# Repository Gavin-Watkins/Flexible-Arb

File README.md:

# Flexible Arduino Due based Arbitrary Signal Generator
Often during a project I have needed a complex test signal that is beyond the capability of the signal or function generators available in my lab. Commercial arbitrary signal generators (ARB) consisting of a fast memory coupled to a digital-to-analogue converter (DAC) are available, but often do not offer the right mix of analog and digital outputs in a suitably flexible (and affordable!) form. This has also been a problem during my day job where I have need to drive a high efficiency radio frequency (RF) power amplifiers (PA) or transmitters with two analogue outputs for the in-phase (I) and quadrature (Q) inputs of an RF modulator and several digital outputs for switching parts of the transmitter. [Previous work used an ARB platform developed around an Arduino Mega2560](https://www.researchgate.net/publication/361063526_A_Digital_Power_Amplifier_for_32-QAM). This was limited to a sample rate of 457kS/s. To increase the sample rate a new ARB has been developed based on an Arduino Due offering up to 8.4MS/s.

The Arduino Due is based on the 32-bit ATSAM3X8E allowing multiple 8-bit DACs and digital outputs to be mapped onto a single port. This ensuring all DAC or digital outputs update at the same time and only a single LUT is call for every update. The Arduino Due also runs at a higher clock rate of 84 MHz. Although 32-bit, none of the four ports (A to D) available on the ATSAM3X8E’s pins map to all 32-bits. Of the four ports, C with 24-bits available is the most useful. These 24 bits in this project are connected to two 8-bit DACs and one 8-bit digital port. However, they could for example drive two 12-bit DACs or any such combination.

# Testing the Arduino Due
The first thing anyone looks at with an ARB is the sampling rate. In a software based ARB like this (as oppose to an FPGA implementation) the microprocessor much fetch the output samples from memory and present them to the port with the DAC. This takes ten instruction cycles resulting in 8.4 MS/s as shown below in the minimum viable code:

start:                                // start of loop  

count = count + 1;                    // increment counter, takes two instruction

count = count & 0x000000FF;           // mask to prevent overflow from end of LUT, takes one instruction

PIOC->PIO_ODSR = Portvalues[count];   // access the LUT and send it to PortC, takes two instructions

goto start;                           // and repeat, takes five instructions

The felixbility of this option opens up other possiblities, like adding a second port which reads from its own LUT. PortA offers 23 bits, which would give a total of 47bits of data. This would however slow down the sample rate to 5.25 MS/s and require external latches for synchronising the data. This ran fastest when in Setup. Putting it in Loop resulted in slowing down. Why this is so, I'm not sure, but it is something I intend to explore further.

# DACs
The most important part of any ARB are the DACs. For this I settle on the DAC0801. Although quite old, they are readily available and easy to interface. Their datasheet quotes a settling time of 100ns consisting of the DAC slewing time and that for any ringing at the output to settle. The slewing time is a factor of the DAC output current and its load impedance. This suggests a maximum sample rate of 10 MS/s, which fits well with the 8.4 MS/s of the Due. The DAC0801 has complementary current sink outputs (pins 2 and 4). The datasheet suggests op-amp active current to voltage (I/V) converters as an output stage. This was found to introduce excess ringing, so passive resistive I/V converters were used instead. With a 1kΩ resistive load (RL) the slew rate was 30V/μs equivalent to a rise and fall time of 42ns. 

The DAC (IC1 and IC3) and op-amp (IC2 and IC4) interface is shown in the Eagle schematic "Sch6.sch" and as a png "Sch6.png". The peak output current of the DAC0801 is set at 2.13mA by the 4k7 resistors on pins 14 and 15 (R10, R14, R19 and R20) when a ±10V power supply is used. A 1k1 resistor tied to 0V and two 4k7 resistors in series (9k4) to +10 V positive supply rail add an offset so the output voltage at pin 4 swings positive and negative around 0V. This is a high impedance port so an op-amp with a gain of 2V/V buffers the output to drive 2V peak-to-peak into a 50Ω load. In the prototype a TL071 proved optimal in terms of bandwidth and ringing. Note in the schematic this is listed as a 741, simply because it was the first op-amp listed. The TL071 has a unity gain bandwidth product of 3MHz, reduced to 1.5MHz with a gain of 2V/V. Other op-amps may provide a better combination of bandwidth, slew rate and output current.

# Code
The Arduino Due can be programmed in the usual Arduino IDE, but has a unique set of instructions which allows direct port access. The following commands setup port C of the Due for direct access: PIOC→PIO_PER and PIOC→PIO_OER. The command PIOC→PIO_ODSR is then used to write data to the port. A goto loop sends data from the LUT to Port C runs in the setup, as using the main Void loop incurs various overheads including the I/O system to check the serial port. The result is 10 instructions and 8.4MS/s output rate. The LUT allocations are accessed by the variable count which is a 32-bit integer. This is masked (by ANDing) with FF (256) in the sinewave example, 1FF (512) in the triple test example and 4FFF (16384) for the 4G Long Term Evolution (LTE) signal example. Restricting the LUT to powers of 2 simplifies (and hence speeds up) the code. For other values an IF or FOR loop could be used to reset count at any value. A noInterrupts command to disable interrupts is included as without it jitter was noted on the output waveform suggesting the compiler sets some interrupts by default. If a lower sample frequency is desired though, the delayMicroseconds command can be included. In this case noInterrupts should be commented out.

# Data Generation
The data for all ports and the trigger signal are stored in a single LUT (Portvalues in the code). For Port C, the bits that are available on the external pins are: bits 1-8 for Ch A DAC, bits 12-19 for Ch B DAC, bits 21-26 for a digital interface and bit 28 as a trigger. These are generated individually and then mapped into a 32bit word which forms the values of Portvalues by multiplying the individual values by an offset and adding them together, for example:

Portvalues[X] = 2^28 x Trigger + 2^21 x Digital + 2^12 x DAC2 + 2 x DAC1

# Tool Chain 
The first two examples were generated in an OpenOffice spreadsheet (File "Signal Gen3.ods) as the LUTs were not very big. The third example was in Python ( due to the resulting LUT size. If using a spreadsheet the data will be generated in a single column. This can be copy and pasted directly into the Arduino IDE as a single column array. It is often more practical though to do this as a 2D array. The values from different cells can be combined with commas as a string into a single cell using the “&” function. In the sinewave example where the values of column Y are to be reformatted into a 16 column by 16 row for 256 values the following is used:

=Y2 & " , " & Y3 & ", " & Y4 & ", " & Y5 & ", " & Y6 & ", " & Y7 & ", " & Y8 & ", " & Y9 & ", " & Y10 & ", " & Y11 & ", " & Y12 & ", " & Y13 & ", " & Y14 & ", " & Y15 & ", " & Y16 & ", " & Y17 & ", "

Using the autofill function will not appropriately increment the Y column values, so there is still quite a bit of manual processing to be done, which is why for larger arrays it is appropriate to use Python. The Python code reads in the File "1M4LTE.txt". The sample rate of the LTE data is 7.68 MS/s, this is the original 122.88 MS/s downsampled by 16. Adding a dummy instruction to the Arduino code results in a sample rate of 7.64 MS/s. This is not close enough to 7.68 MS/s for standard compliance, but sufficient for measuring the adjacent channel power ratio (ACPR) of a PA/transmitter output.

# Hardware Implementation
To verify the concept, an Arduino Due “shield” was produced. This was fabricated on standard FR4 substrate using through hole DIL components. The layout is shown in "Sch6.brd" for Eagle and "Sch6_PCB.png" as a png. The Gerber files are in the zip file "Gerbers.zip". DIL components incur stray inductance and capacitance when operating in the MHz region, but allow the design to be easily modified. A surface mount implementation would probably produce better results than those presented here. 

The shield runs off a 5V supply for the digital and +/-10V for the analogue. The former can be extracted from the USB interface, as it is assumed that this project will be permanently connected to a computer for updating the LUT. The +/-10V can be derived from the 5V USB with a DC-DC converter and then smoothing and filtering.

# Example Results
The code includes three examples: a 32.8125kHz quadrature sinewave on DAC1 and DAC2 with a 256 value LUT (8.4MS/s / 256 = 32.8125 kHz), a triple tone test at around 1 MHz and the 4G LTE signal generation. Screen captures of these are shown to demonstrate the capabilities of the ARB. For the triple tone test the three tone frequencies are 984.375 kHz, 1.00078125 MHz and 1.0171875 MHz. These three resulting frequencies (Fr) were calculated with:

Fr = Fs * n / LUTs

Where Fs is the sampling frequency, n a whole number to avoid discontinuities – reducing spurious produces – and LUTs the LUT size. For an Fs was 8.4MS/s, n: 60, 61 and 62, and LUTs 512. Even with all the harmonically related spurious products, they are -38dB relative to the three tones. A higher resolution DAC would offer greater dynamic range, and hence lower spurious products. 

For the LTE signal, a screen capture of the spectrum of the I-channel signal is included. This includes guard channels, resulting in an actual RF bandwidth is 1.08MHz (consisting of six 180kHz resource blocks). The baseband bandwidth is half this, a spectrum of 504kHz as clearly shown in the example. The spectral regrowth is partially due to DAC non-linearities and also spurious products introduced by the system. uffers. The next phase of this research is to combine the LTE signal generator with a low-cost quadrature modulator development board to generate 4G signals for testing transmitter architectures.

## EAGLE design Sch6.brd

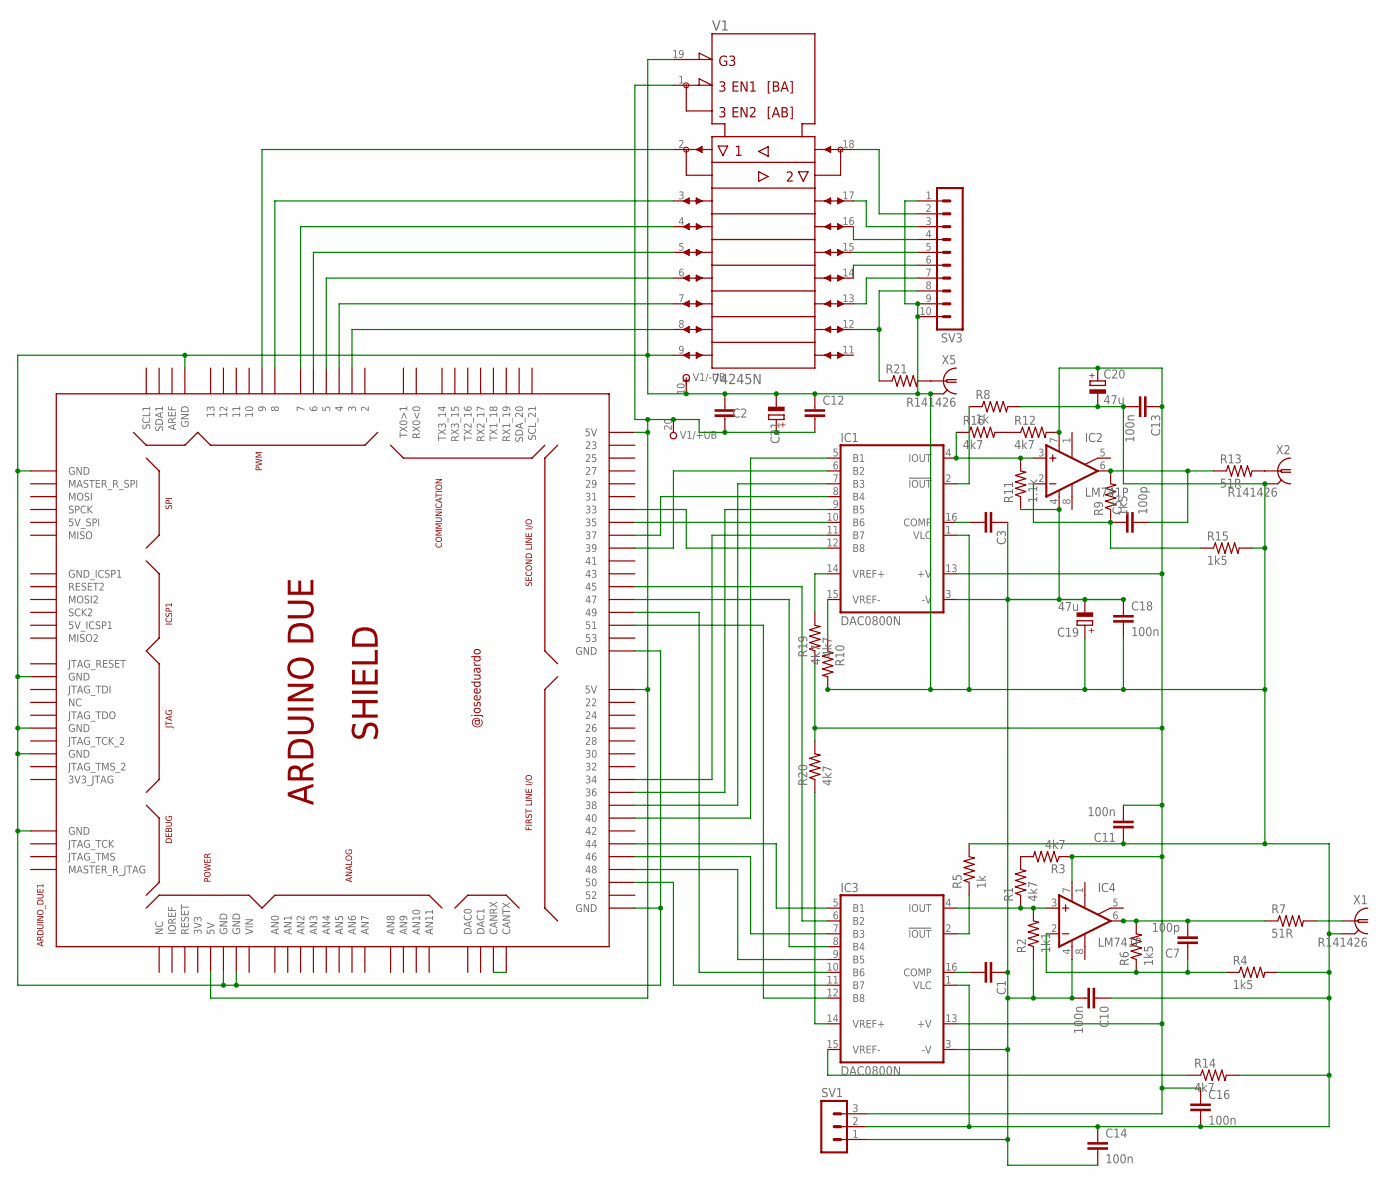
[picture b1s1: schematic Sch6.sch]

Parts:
ARDUINO_DUE1: ARDUINO_DUE_SHIELD
C1, C2, C3, C12: C-EU050-025X075; C050-025X075
C5, C7: 100p; C050-025X075
C10, C11, C13, C14, C16, C18: 100n; C050-025X075
C19, C20: 47u; E5-10,5
C21: CPOL-EUE5-10.5; E5-10,5
IC1, IC3: DAC0800N; DIL16
IC2, IC4: LM741P; DIL08
R1, R3, R10, R12, R14, R16, R19, R20: 4k7; 0207/10
R2: 1k1; 0207/10
R4, R6, R9, R15: 1k5; 0207/10
R5, R8: 1k; 0207/10
R7, R13: 51R; 0207/10
R11: 1.1k; 0207/10
R21: R-US_0207/10; 0207/10
SV1: MA03-1
SV3: MA10-1
V1: 74245N; DIL20
X1, X2, X5: R141426

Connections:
unnamed: ARDUINO_DUE1.51, IC3.12 (B8)
unnamed: R21.2, X5.1
unnamed: ARDUINO_DUE1.33, IC1.12 (B8)
unnamed: IC1.2 (!IOUT), R8.1
unnamed: ARDUINO_DUE1.9, V1.2 (A1)
unnamed: ARDUINO_DUE1.34, IC1.11 (B7)
unnamed: ARDUINO_DUE1.50, IC3.11 (B7)
unnamed: ARDUINO_DUE1.35, IC1.10 (B6)
unnamed: ARDUINO_DUE1.36, IC1.9 (B5)
unnamed: ARDUINO_DUE1.37, IC1.8 (B4)
unnamed: ARDUINO_DUE1.49, IC3.10 (B6)
unnamed: ARDUINO_DUE1.CANRX, ARDUINO_DUE1.CANTX
unnamed: ARDUINO_DUE1.5V0 (5V), ARDUINO_DUE1.5V0_1 (5V), ARDUINO_DUE1.5V0_2 (5V), C2.2, C12.2, C21.+, V1.1 (DIR), V1.20 (+UB)
unnamed: ARDUINO_DUE1.38, IC1.7 (B3)
unnamed: ARDUINO_DUE1.39, IC1.6 (B2)
unnamed: ARDUINO_DUE1.8, V1.3 (A2)
unnamed: ARDUINO_DUE1.40, IC1.5 (B1)
unnamed: ARDUINO_DUE1.48, IC3.9 (B5)
unnamed: ARDUINO_DUE1.47, IC3.8 (B4)
unnamed: R1.2, R3.2
unnamed: ARDUINO_DUE1.45, IC3.6 (B2)
unnamed: IC3.4 (IOUT), IC4.3 (+IN), R1.1, R2.2
unnamed: ARDUINO_DUE1.7, V1.4 (A3)
unnamed: ARDUINO_DUE1.6, V1.5 (A4)
unnamed: ARDUINO_DUE1.5, V1.6 (A5)
unnamed: ARDUINO_DUE1.4, V1.7 (A6)
unnamed: ARDUINO_DUE1.3, V1.8 (A7)
unnamed: SV3.5, V1.15 (B4)
unnamed: SV3.6, V1.14 (B5)
unnamed: SV3.7, V1.13 (B6)
unnamed: R21.1, SV3.8, V1.12 (B7)
unnamed: SV3.4, V1.16 (B3)
unnamed: SV3.3, V1.17 (B2)
unnamed: SV3.2, V1.18 (B1)
unnamed: C11.2, C13.1, C16.1, C20.+, IC1.13 (+V), IC2.7 (V+), IC3.13 (+V), IC4.7 (V+), R3.1, R12.2, R19.1, R20.2, SV1.3
unnamed: ARDUINO_DUE1.GND, ARDUINO_DUE1.GND_1 (GND), ARDUINO_DUE1.GND_2 (GND), ARDUINO_DUE1.GND_3 (GND), ARDUINO_DUE1.GND_4 (GND), ARDUINO_DUE1.GND_5 (GND), ARDUINO_DUE1.GND_7 (GND), ARDUINO_DUE1.GND_8 (GND), ARDUINO_DUE1.GND_9 (GND), ARDUINO_DUE1.GND_10 (GND), C2.1, C10.1, C11.1, C12.1, C13.2, C14.1, C16.2, C18.2, C19.+, C20.-, C21.-, IC1.1 (VLC), IC3.1 (VLC), R4.2, R5.2, R8.2, R10.2, R14.2, R15.2, SV1.2, SV3.1, SV3.9, SV3.10, V1.9 (A8), V1.10 (-UB), V1.19 (!G), X1.2, X1.3 (2), X1.4 (2), X1.5 (2), X2.2, X2.3 (2), X2.4 (2), X2.5 (2), X5.2, X5.3 (2), X5.4 (2), X5.5 (2)
unnamed: R12.1, R16.2
unnamed: ARDUINO_DUE1.46, IC3.7 (B3)
unnamed: C3.2, IC1.16 (COMP)
unnamed: ARDUINO_DUE1.44, IC3.5 (B1)
unnamed: C1.2, IC3.16 (COMP)
unnamed: C5.1, IC2.2 (-IN), R9.1, R15.1
unnamed: IC1.4 (IOUT), IC2.3 (+IN), R11.2, R16.1
unnamed: C7.1, IC4.2 (-IN), R4.1, R6.1
unnamed: IC3.2 (!IOUT), R5.1
unnamed: C1.1, C3.1, C10.2, C14.2, C18.1, C19.-, IC1.3 (-V), IC2.4 (V-), IC3.3 (-V), IC4.4 (V-), R2.1, R11.1, SV1.1
unnamed: C7.2, IC4.6 (OUT), R6.2, R7.1
unnamed: R7.2, X1.1
unnamed: C5.2, IC2.6 (OUT), R9.2, R13.1
unnamed: R13.2, X2.1
unnamed: IC1.15 (VREF-), R10.1
unnamed: IC3.15 (VREF-), R14.1
unnamed: IC1.14 (VREF+), R19.2
unnamed: IC3.14 (VREF+), R20.1

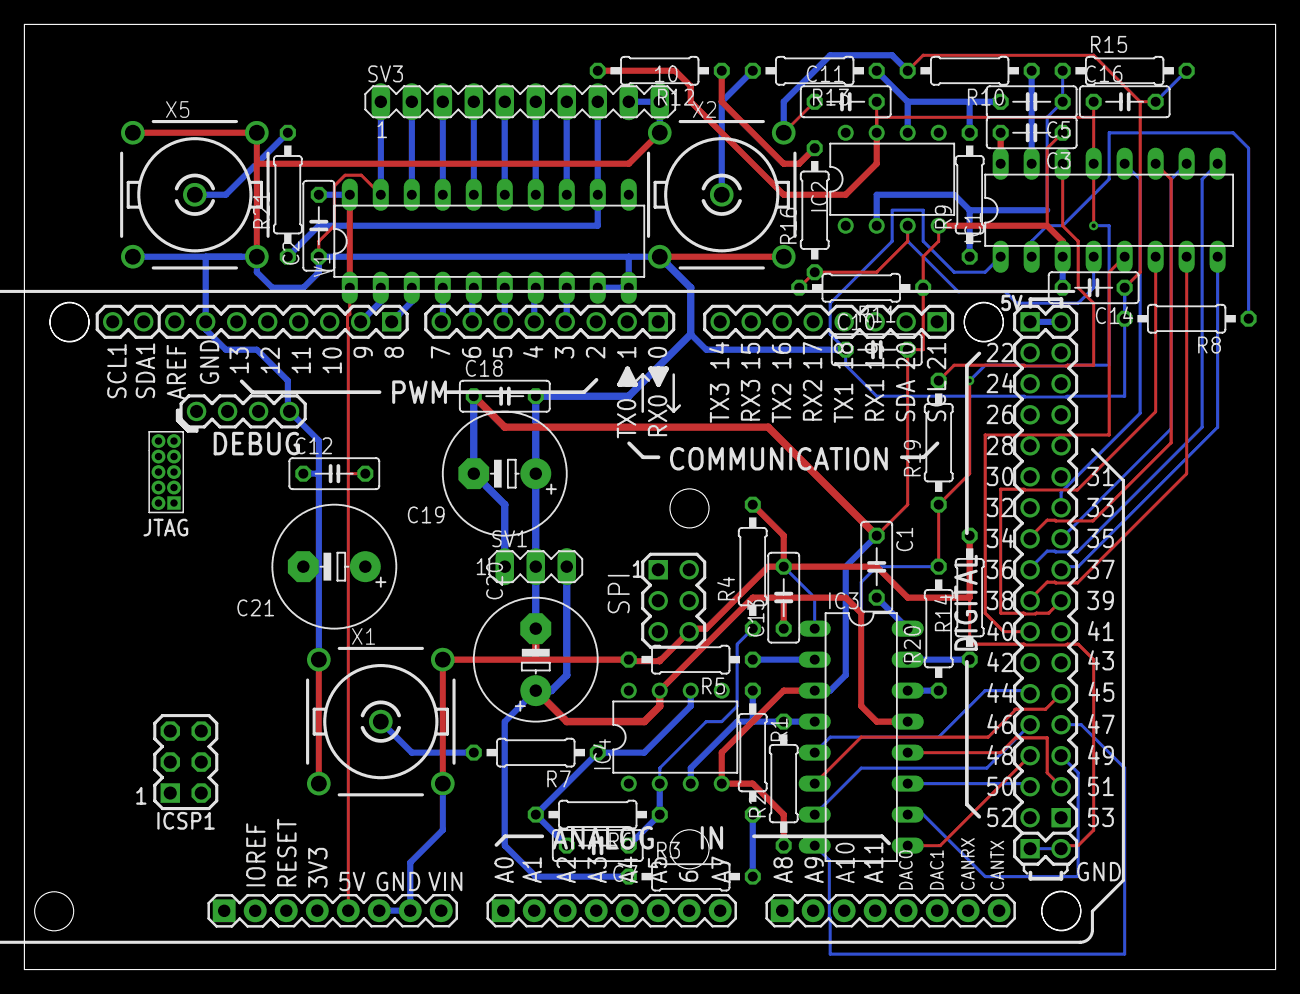
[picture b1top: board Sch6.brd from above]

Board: 2 copper layers, 102.5 x 77.5 mm, 45 parts (0 on the bottom side), 54 nets.
